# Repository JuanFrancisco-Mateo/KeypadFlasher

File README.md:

# KeypadFlasher

This project contains custom firmware compatible with a number of different CH55x based programmable keypads found on sites like Aliexpress and Amazon.

## TODO

This project is work in progress, what's left to do:
- Build an adapter to easily enter bootloader mode without opening the device up or making the contraption manually

## Usage

Don't have a keypad yet? See the [supported devices](#supported-devices) section for some compatible options.

Please see the [development](#development) section for instructions on manually building the project from source.

If you just want to use it, visit https://keypad-flasher.amyjeanes.com for the hosted version of the web app in a WebUSB compatible browser (anything based on Chromium, e.g. Chrome, Edge, Opera)

You will need to ensure the device is plugged in while in bootloader mode to be recognised and flashed by the app.

I am currently building a simple adapter you can plug into the device in between the USB cable and the keypad that will allow you to easily enter bootloader mode without opening the device up. If you would like one of these adapters, please contact me via email (see my GitHub profile). I will update this README when they are available for purchase.

In the mean time, you can enter bootloader mode by creating the following contraption manually, many thanks to [@dzid26](https://github.com/dzid26) for helping out with this:

You will need:
- A USB-C male to female breakout board with headers
  - Some options here, make sure they are male to female:
    - https://www.aliexpress.com/item/1005009136277062.html
    - https://www.amazon.co.uk/Nicear-Type-C-Double-Sided-Connector-Transfer/dp/B0F1Y43GY3
    - https://www.ebay.co.uk/itm/194958873406?var=495399427358
- 4 male to female jumper wires
- 2 10k ohm resistors
- A breadboard

Wiring guide:
- Consider the 2 10k ohm resistors as R1 and R2
- Consider the 4 jumpers as J1, J2, J3 and J4 and JXM as the male end and JXF as the female end of each jumper (e.g. J1F is female, J1M is male)
- Plug the USB-C breakout board into the keypad's USB-C female port
- **Do not** plug in the USB cable into your computer yet
- Connect J1M and J2M to opposite sides of a breadboard row
- Connect one end of R1 next to J1M and the other end next to J2M
- Repeat this with J3M, J4M and R2 on another breadboard row
- Connect J1F to the VCC pin on one side of the USB-C breakout board
- Connect J2F to the D+ pin on the same side of the USB-C breakout board
- Repeat this on the other side of the USB-C breakout board with J3F and J4F
  - This is needed due to the reversible nature of USB-C connectors

It should end up look something like this:

Essentially, we are shorting D+ to VCC on both sides of the USB-C breakout board using 10k ohm resistors when the device is powered on, which forces it into bootloader mode.

You could also make a version of this with a USB-A 2.0+ breakout board too which you could use with a USB-A to USB-C cable if you have one of those instead.

To verify whether your device is in HID (default) mode or bootloader mode on Windows, you can run in PowerShell the following snippet:

```powershell
$devices = (Get-CimInstance -ClassName CIM_LogicalDevice).DeviceID; if(($devices | ? { $_.Contains("VID_1209&PID_C55D") })) { "HID mode" } elseif (($devices | ? { $_.Contains("VID_4348&PID_55E0")})) { "bootloader mode" } else { "device not found" }
```

On Linux, you can use `lsusb` and look for either of these IDs:
- HID mode: `1209:C55D`
- Bootloader mode: `4348:55E0`

Once the device is in bootloader mode, we can connect to it using the web app on Windows / Mac / Linux / Android, except if you're on Windows devices which need one more step.

On Windows, you will need to install a driver for the CH55x bootloader to be recognised. You can use [Zadig](https://zadig.akeo.ie/) to install the "WinUSB" driver for the device (will likely show up as Unknown Device #1) when in bootloader mode.

Please note that the CH55x bootloader on some devices has a quirk where it will only stay in bootloader mode for about 10 seconds after being plugged in, so you may need to be quick to connect to it in the web app. Once connected you get a few minutes to actually flash the firmware, but that will eventually time out as well. It may also still show as being in bootloader mode from a USB perspective even after timing out, so if you cannot connect, unplug and replug the device to re-enter bootloader mode.

Now you can hopefully connect to the device in the app and flash the new firmware! If you cannot see any devices in the connection window, please ensure that the device is connected in bootloader mode and that you have the correct drivers installed (on Windows).

At this time there is only very basic firmware that is designed for keypads with 1 knob and 3 buttons but this will be updated soon to handle different layouts and actually allow remapping of keys etc. The current firmware will just register the 3 buttons as Ctrl-C, Ctrl-V and Ctrl-Z and the knob as scroll up/down.

Please note that the original firmware on the device will be lost when you flash this custom firmware, so only proceed if you are okay with that.

## Supported devices

The following is a list of tested and known compatible devices, but other devices using the CH55x series microcontrollers may also work.

They all have USB-C connectors unless otherwise noted:

- [2 Keys](https://www.aliexpress.com/item/1005004970126333.html?spm=a2g0o.order_detail.order_detail_item.3.3c7af19cNrdJJB)
  - Uses non-standard LEDs that are not compatible with this project's NeoPixel support so LED functionality will not work
- [3 Keys 1 Knob](https://www.aliexpress.com/item/1005006627901462.html?spm=a2g0o.order_detail.order_detail_item.3.295bf19c3IDC8m)
- [4 Keys](https://www.aliexpress.com/item/1005008020501723.html?spm=a2g0o.order_detail.order_detail_item.3.7d51f19cZTzoOY)
- [6 Keys 1 Knob](https://www.aliexpress.com/item/1005009812219099.html?spm=a2g0o.order_detail.order_detail_item.3.6afff19cXlayc4)
- [6 Keys 1 Knob (Sikai)](https://sikaicase.com/products/6key-usb-c-macro-programmable-keyboard-osu-one-handed-mechanical-keyboard-with-knobs-6-fully-programmable-keys-hotkeys-rgb-backlit-mini-keypad-for-pc-gamer-1)
- [10 Keys](https://www.aliexpress.com/item/1005005509140217.html?spm=a2g0o.order_detail.order_detail_item.7.3c7af19cNrdJJB)
  - Uses a Micro-USB connector, will need a Micro-USB to USB-C adapter and USB-C cable to use the bootloader adapter / contraption above
  - Uses fixed blue LEDs that are always on and cannot be controlled by the firmware

## Unsupported devices

These devices have been tested and found to use different types of microcontrollers, and are not compatible with this firmware:

- [9 Keys](https://www.aliexpress.com/item/1005005307250747.html?spm=a2g0o.order_detail.order_detail_item.5.3c7af19cNrdJJB)
  - Uses a CH32V203 microcontroller
  - Can remap keys using https://sayodevice.com/ web-based flasher (similar to this project!)
- [12 Keys 2 Knobs](https://www.aliexpress.com/item/1005007160113318.html?spm=a2g0o.order_detail.order_detail_item.3.5bd6f19cdqcQwn)
  - Uses a CH579M microcontroller
  - Can remap keys using https://github.com/kriomant/ch57x-keyboard-tool or other CH57x programming tools

## Adding support for new keypads

- Connect the keypad in bootloader mode with the web app. Turn on Development mode to see the bootloader ID in the detected device card (e.g. `Bootloader 2.31 · ID 126, 80, 44, 189`). Copy those four numbers.
- Turn on **Debug firmware (USB CDC)** in the app and click **Compile & Flash**. Debug firmware works without a known config and exposes a USB serial port; it prints a banner, per-pin snapshots, and a 1s summary so you can see which pins change when you press buttons or rotate the encoder.
- Open a serial terminal to the new USB CDC device (baud rate does not matter) and press buttons/rotate the knob. Notes from the log:
  - Pins are labelled `P<port>.<bit>` (e.g. `P3.2` for pin `32`).
  - `active_low` means the signal reads low when pressed; `active` shows whether the firmware considers the input asserted.
  - Lines marked `configured` came from an existing config; unmarked lines help you find unused pins.
- Add an entry keyed by the bootloader ID to [src/Keypad.Flasher.Client/src/lib/keypad-configs.ts](src/Keypad.Flasher.Client/src/lib/keypad-configs.ts). Provide a friendly `name`, fill `buttons` with pin numbers, `activeLow`, optional `ledIndex`, `bootloaderOnBoot`, and `bootloaderChordMember`, add any `encoders`, and set `neoPixelPin` (or `-1` if none). Example:

```ts
"126-80-44-189": {
  name: "3 Keys 1 Knob",
  config: {
    buttons: [
      { pin: 33, activeLow: true, ledIndex: -1, bootloaderOnBoot: true, bootloaderChordMember: false, function: { type: "Sequence", sequence: "enter", delay: 5 } },
    ],
    encoders: [
      { pinA: 31, pinB: 30, clockwise: { type: "Function", functionPointer: "hid_consumer_volume_up" }, counterClockwise: { type: "Function", functionPointer: "hid_consumer_volume_down" } },
    ],
    neoPixelPin: 34,
  },
},
```

- Reflash without the debug checkbox to validate the mapping, then open a PR adding the new config so others can use it.

## Development

To build and run the project from source, you will need:
- Visual Studio Code
- .NET 10 SDK
- Node.js v22+
- Arduino IDE with arduino-cli installed and on the system PATH

First time setup:
```bash
arduino-cli core install CH55xDuino:mcs51
git clone https://github.com/AmyJeanes/KeypadFlasher
cd KeypadFlasher/src/Keypad.Flasher.Client
npm install
```

Compile device firmware manually:
```bash
cd src/Keypad.Firmware
arduino-cli compile --fqbn CH55xDuino:mcs51:ch552:usb_settings=user148,clock=16internal --export-binaries
```

You can also configure the Arduino IDE and use that to compile and upload the firmware if you prefer a GUI:
- Open Arduino IDE
- Open the `src/Keypad.Firmware/Keypad.Firmware.ino` project
- Select the board "CH55xDuino" on Tools > Board
- Select "P3.6 (D+) Pull up" on Tools -> Bootloader
- Select "16MHz Internal 3.5V or 5V" on Tools -> Clock
- Select "USB" on Tools -> Upload method
- Select "USER CODE w/148B USB RAM" on Tools -> USB Settings
- Compile the project
- Connect the device in bootloader mode
- Upload the firmware (note: original firmware will be lost!)

Run the web app locally:
```
dotnet run --project src/Keypad.Flasher.Server
```

or

Build and run docker image:
```
docker build -t keypad -f ./src/Keypad.Flasher.Server/Dockerfile ./src
docker run -p 54196:8080 --rm -it -m 256MB keypad
```

If the browser does not open automatically, open a Chromium-based browser and navigate to `http://localhost:54196`

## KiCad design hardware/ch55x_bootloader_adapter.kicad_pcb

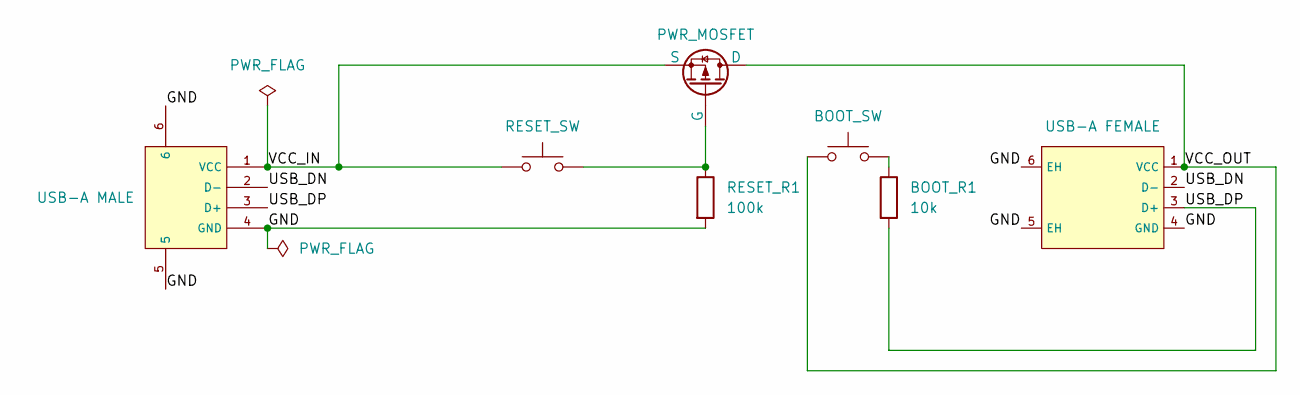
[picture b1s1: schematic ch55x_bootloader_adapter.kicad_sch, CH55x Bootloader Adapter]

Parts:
BOOT1: BOOT_SW; SW-SMD_4P-L6.2-W6.2-P4.00-LS9.5-TL
BOOT_R1: 10k; R_0805_2012Metric
RESET1: RESET_SW; SW-SMD_4P-L6.2-W6.2-P4.00-LS9.5-TL
RESET_MOSFET1: PWR_MOSFET; SOT-23
RESET_R1: 100k; R_0805_2012Metric
USB-A-F1: USB-A FEMALE; USB-A-SMD_U-A-24SS-W-2; LCSC C530629
USB-A-M1: USB-A MALE; USB-A-TH_U-G-04WD-W-01; LCSC C98125

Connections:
/GND: RESET_R1.2, USB-A-F1.4 (GND), USB-A-F1.5 (EH), USB-A-F1.6 (EH), USB-A-M1.4 (GND), USB-A-M1.5, USB-A-M1.6
/USB_DN: USB-A-F1.2 (D-), USB-A-M1.2 (D-)
/USB_DP: BOOT_R1.2, USB-A-F1.3 (D+), USB-A-M1.3 (D+)
/VCC_IN: RESET1.1, RESET_MOSFET1.2 (S), USB-A-M1.1 (VCC)
/VCC_OUT: BOOT1.1, RESET_MOSFET1.3 (D), USB-A-F1.1 (VCC)
unnamed: BOOT1.2, BOOT_R1.1
unnamed: RESET1.2, RESET_MOSFET1.1 (G), RESET_R1.1

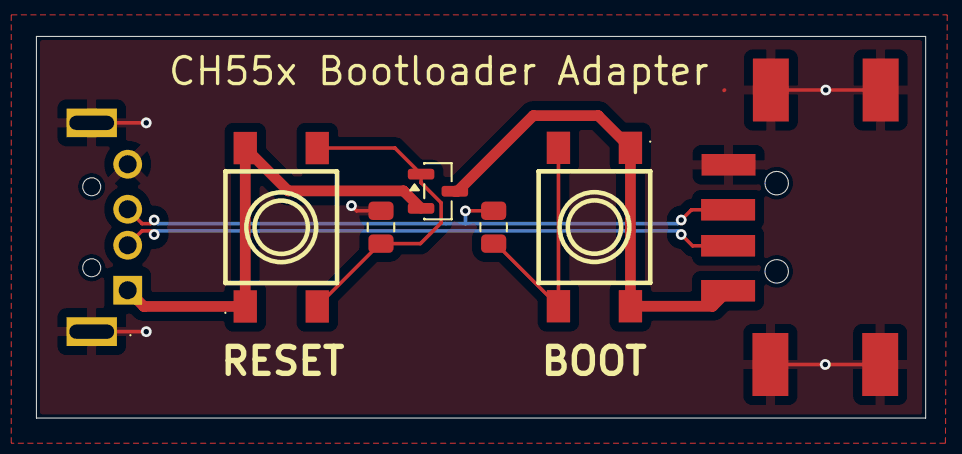
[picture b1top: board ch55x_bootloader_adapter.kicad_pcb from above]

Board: 2 copper layers, 49.4 x 21.2 mm, 7 parts (0 on the bottom side), 7 nets.

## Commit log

2025-12-14 reoder
2025-12-14 update title
2025-12-14 Update README with USB-C cable requirement
2025-12-14 clarify
2025-12-14 Clarify instructions for adding compatible devices
2025-12-14 Add note about supported devices in README
2025-12-16 cleanup unused parts of the code
2025-12-17 prepare for generation of configuration.c/h by moving non essentials out
2025-12-17 generate configuration
2025-12-17 run tests on build
2025-12-17 rename
2025-12-17 add test project to slnx
2025-12-17 improve tests and fix wrong neopixel count
2025-12-17 fix up more stuff, add usb serial debug mode, add proper config for 6 button 1 enc
2025-12-17 back to default 4 key 1 encoder config and set up more sensible config for supported keypads
2026-01-05 small tweaks
2026-01-05 auto set configuration for detected keypad type, prevent keypad firmware flashing (except debug mode) and add info for unsupported devices
2026-01-05 much improved UI and add pixel reverse support
2026-01-05 fix bootloader config for 6 keys 1 knob
2026-01-05 add new icons and title
2026-01-06 split devices into hardware and bindings
2026-01-06 add UI for displaying and editing button layouts
2026-01-06 consolidate everything and add mouse controls too
2026-01-06 various fixes and improvements
2026-01-06 update todo
2026-01-06 improve UI for selecting key, allow selection of more keys and have dropdown for manual selection or mobile suport
2026-01-06 add missing media key functions
2026-01-06 ping keep alive device, handle disconnects much better and allow configuration of bootloader chord/boot keys
2026-01-06 copy/paste/dragndrop and various big ui improvements
2026-01-06 ui improvements
2026-01-06 remember last active layout on load
2026-01-06 add demo feature
2026-01-06 fix interaction in collapsible steps
2026-01-06 refactor code into components and stuff
2026-01-06 refactor
2026-01-06 small details
2026-01-06 more ui improvements
2026-01-06 basic lighting customization
2026-01-06 refactor lighting to be individual to the keys
2026-01-06 Improve lighting UI
2026-01-06 add import/export
2026-01-06 big ui improvements, pretty much feature complete
2026-01-06 more ui tweaks
2026-01-06 final style tweak
2026-01-06 various ui tweaks
2026-01-06 more layout improvements
2026-01-07 new lighting effects and lighting preview
2026-01-07 cleanup overvalidation mess
2026-01-07 trip down firmware a bit
2026-01-07 some improvements to step clipboard and stuff
2026-01-07 fix title
2026-01-07 flip around 2 key layout pins
2026-01-07 show bootloader chords on main layout page
2026-01-07 use link icon instead much more visible
2026-01-07 move bootloader config to icons
2026-01-07 move global lighting settings to new button
2026-01-07 improve status bar
2026-01-07 fixup touch inputs for bootloader flag keys
2026-01-15 Update keypad-configs.ts
    Added support for 6 Key 1 Knob from Sikai
    - Top buttons: Previous / Play / Next
    - Down buttons: Crtl + C / Crtl + X / Crtl + V
    - Knob: Volume control / Mute
2026-01-16 fix double tap issue on no led disabled button
2026-01-16 fix bootloader config and add toasts for notifications on main screen
2026-01-16 make encoder size match two stacked buttons again
2026-01-16 greatly improve keyboard capture UX
2026-01-16 make warning red for no boot entry
2026-01-16 remove usage of any and cleanup unneeded legacy handling
2026-01-16 fix build
2026-01-16 hide sikai 6 keys 1 knob from demo mode
2026-01-16 add to readme and rename slightly
2026-01-16 fix and improve debug mode, add signal filtering on by default
2026-01-18 add wip bootloader adapter design
2026-01-18 update adapter pcb
2026-01-19 more hardware progress
2026-01-19 change adapter to be USB-A instead for simplicity and cost
2026-01-19 swap to new buttons and improve layout further
2026-01-19 setup fab toolkit
2026-01-19 set board height to 1.6mm default
2026-01-19 minor tweaks to adapter, added instructions on back of it
2026-01-19 improve position of github link
2026-01-19 minor tweaks to text positioning
2026-01-19 only run CI when relevant parts have changed
2026-01-19 move source code to src folder
2026-01-19 fixup build and gitignore
2026-01-19 remove unused usb-c plug step file
2026-01-19 give slightly more spacing around a VCC wire
